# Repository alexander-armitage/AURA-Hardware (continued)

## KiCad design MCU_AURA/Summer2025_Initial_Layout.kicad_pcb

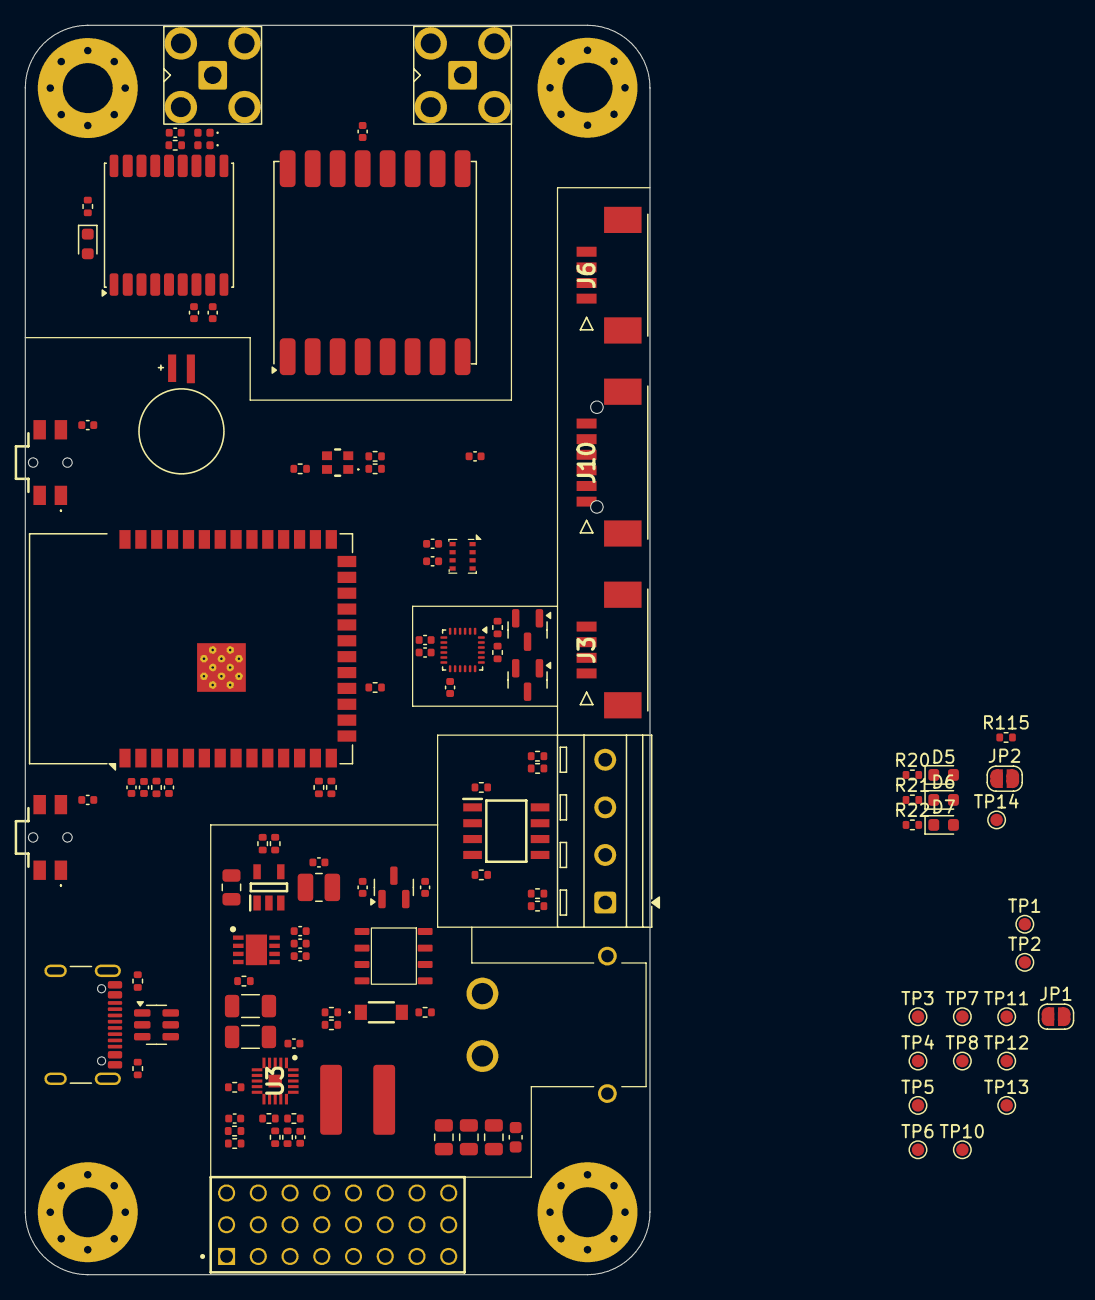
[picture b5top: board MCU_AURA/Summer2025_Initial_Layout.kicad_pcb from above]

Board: 4 copper layers, 50.0 x 100.0 mm, 123 parts (1 on the bottom side), 76 nets, no tracks yet.

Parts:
BT1: MS621FE-FL11E; BAT_MS621FE-FL11E
C22, C25, C27, C38, C39, C41, C42, C43, C44, C45, C104, C108, C109, C201, C203, C204: 100n; C_0402_1005Metric
C100, C113, C114: 1u; C_0402_1005Metric
C101, C102: 22u; C_1206_3216Metric
C103: 18n; C_0402_1005Metric
C105, C106, C107: 22u; C_0805_2012Metric
C110, C112, C202: 10u; C_0402_1005Metric
C111: 4u7; C_0805_2012Metric
C115: 100n; C_0603_1608Metric
C200: 22u; C_0402_1005Metric
D1: NH-B2020RGBA-HF; NHB2020RGBAHF
D4, D5, D6, D7: LED; LED_0603_1608Metric
D101: MMSZ5242B; MMSZ5252B
D503490: D_0402_1005Metric
H1, H2, H3, H4: MountingHole_Pad; MountingHole_4mm_Pad_Via
J1, J2: SMA_Connector
J3, J6: 532617004
J4: TF-CARD_H1.8; TFCARDH18
J5: TSW-108-07-G-T; SAMTEC_TSW-108-07-G-T
J10: 532617006
J100: XT30PW-M; XT30PWM
J101: USB_C_Receptacle_USB2.0_16P; USB_C_Receptacle_GCT_USB4105-xx-A_16P_TopMnt_Horizontal
J400: Screw_Terminal_01x04; TerminalBlock_MetzConnect_Type086_RT03404HBLC_1x04_P3.81mm_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
JP1, JP2: SolderJumper_2_Bridged; SolderJumper-2_P1.3mm_Open_RoundedPad1.0x1.5mm
L4: 27nH; LED_0402_1005Metric
L100: 1u8; CKST0603-1.5uHM
L101: 2u2; L_1008_2520Metric
Q1, Q2: BSS138; SOT-23
R18, R19, R22: 1k; R_0402_1005Metric
R20, R21: 4k7; R_0402_1005Metric
R25, R26, R27, R200, R402, R405: 10k; R_0402_1005Metric
R36: 100R; R_0402_1005Metric
R37: 120R; R_0402_1005Metric
R38: 270R; R_0402_1005Metric
R100: 100k; R_0402_1005Metric
R101: 49k; R_0402_1005Metric
R102: 13k; R_0402_1005Metric
R103: 180k; R_0402_1005Metric
R104: 33k; R_0402_1005Metric
R105: 330k; R_0402_1005Metric
R106: 110k; R_0402_1005Metric
R107: 15k; R_0402_1005Metric
R108, R109: 5k1; R_0402_1005Metric
R110: 680R; R_0402_1005Metric
R111: 540k; R_0402_1005Metric
R112: 120k; R_0402_1005Metric
R113, R115, R400, R403: 220k; R_0402_1005Metric
R114, R401, R404: 22k; R_0402_1005Metric
R201, R202: 0R; R_0402_1005Metric
S3, S4: EVQ-PUC02K; EVQPUC02K
TP1, TP2, TP3, TP4, TP5, TP6, TP7, TP8, TP10, TP11, TP12, TP13, TP14: TestPoint; TestPoint_Pad_D1.0mm
U1: SI4825DDY-T1-GE3
U2: RFM95W-868S2; HOPERF_RFM9XW_SMD
U3: TPS56C230RJER; QFN45P300X300X100-21N-D
U11: ICM-20948; InvenSense_QFN-24_3x3mm_P0.4mm
U12: BMP280; Bosch_LGA-8_2x2.5mm_P0.65mm_ClockwisePinNumbering
U13: MAX-M10S; ublox_MAX
U101: TPS2115ADRBR; SON65P300X300X100-9N-D
U102: TLV62566DBVR; SOT95P280X145-5N
U103: AP2127N-1.8; SOT-23
U200: ESP32-S3-WROOM-1
U201: USBLC6-2SC6; SOT-23-6
U400: DMN6040SSD-13; SOIC127P600X170-8N

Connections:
+1V8: C42.1, C45.1, C114.1, Q1.1 (G), Q2.1 (G), R26.2, R27.2, TP11.1, U11.8 (VDDIO), U11.13 (VDD), U11.22 (~CS), U103.2 (VO)
+3V3: C22.1, C25.1, C27.1, C38.1, C39.1, C44.1, C112.1, C113.1, C200.1, C201.1, D1.3 (VIN), D7.2 (A), J3.1, J4.4 (VDD), J10.1, L101.2, R25.2, R111.2, R200.2, TP13.1, U2.13 (3.3V), U12.2 (CSB), U12.6 (VDDIO), U12.8 (VDD), U13.7 (VCC_IO), U13.8 (VCC), U103.3 (VI), U200.2 (3V3)
+5V: C105.1, C106.1, C107.1, C109.1, C115.1, D5.2 (A), J5.02, J5.05, J5.08, J5.11, J5.14, J5.17, J5.20, J5.23, JP1.1 (A), L100.2, R106.2, TP6.1, U101.6 (IN2)
+5V_FILT: C110.1, C111.1, D6.2 (A), JP1.2 (B), JP2.2 (B), TP8.1, U101.7 (OUT), U102.1 (EN/PG), U102.4 (VIN)
+BATT: J100.1, J400.2, J400.4, U1.1, U1.2, U1.3
+BATT_FILT: C101.1, C102.1, D101.1 (K), R101.2, R113.2, U1.5, U1.6, U1.7, U1.8, U3.2 (VIN_1), U3.3 (VIN_2), U3.4 (VIN_3), U3.5 (VIN_4)
+VCC_RF: R19.2, U13.14 (VCC_RF)
+VUSB: C108.1, J101.A4 (VBUS), J101.A9 (VBUS), J101.B4 (VBUS), J101.B9 (VBUS), JP2.1 (A), R115.2, TP10.1, U101.3 (D1), U101.8 (IN1), U201.5 (VBUS)
/Actuation Control/GND_PY1: J400.1, R400.2, U400.7, U400.8
/Actuation Control/GND_PY2: J400.3, R403.2, U400.5, U400.6
/Digital_Peripherals/REGOUT: C41.1, U11.10 (REGOUT)
/Digital_Peripherals/SCL_1V8: Q1.2 (S), R26.1, TP1.1, U11.23 (SCL/SCLK)
/Digital_Peripherals/SDA_1V8: Q2.2 (S), R27.1, TP2.1, U11.24 (SDA/SDI)
/ESP32/D+: R202.2, U200.14 (USB_D+)
/ESP32/D-: R201.2, U200.13 (USB_D-)
/ESP32/EN: C202.1, C204.1, R200.1, S4.3 (NO_2), U200.3 (EN)
/ESP32/RST: C203.1, S3.3 (NO_2), U200.27 (IO0)
/ESP32/USB_MCU_D+: R202.1, U201.4 (I/O2)
/ESP32/USB_MCU_D-: R201.1, U201.6 (I/O1)
/Power/3V3_LED: D7.1 (K), R22.2
/Power/5V_FILT_LED: D6.1 (K), R21.2
/Power/5V_LED: D5.1 (K), R20.2
/Power/BST_5V: C104.1, U3.1 (BST)
/Power/CC1: J101.A5 (CC1), R108.2
/Power/CC2: J101.B5 (CC2), R109.2
/Power/EN_5V: R101.1, R102.2, TP4.1, U3.12 (EN)
/Power/FB_3V3: R111.1, R112.2, TP12.1, U102.5 (FB)
/Power/FB_5V: R106.1, R107.2, TP5.1, U3.14 (FB)
/Power/MODE: R103.1, R104.2, U3.15 (MODE)
/Power/PGOOD: R105.1, TP3.1, U3.9 (PGOOD)
/Power/SS_5V: C103.1, U3.11 (SS)
/Power/SW_3V3: L101.1, U102.3 (SW)
/Power/SW_5V: C104.2, L100.1, U3.6 (SW_1), U3.19 (SW_2), U3.20 (SW_3)
/Power/VCC: C100.1, R103.2, R105.2, U3.17 (VCC)
/Power/rvrs_plr: D101.2 (A), R100.2, TP7.1, U1.4
/RF_Peripherals/GPS_IND: C43.1, L4.2, R19.1
/RF_Peripherals/GPS_LED: D4.1 (K), R18.2
/RF_Peripherals/GPS_RF_IN: D503490.1 (K1), J2.1, L4.1, U13.11 (RF_IN)
/RF_Peripherals/LOCK_PULSE: D4.2 (A), U13.4 (TIMEPULSE)
/RF_Peripherals/LORA_ANT: J1.1, U2.9 (ANT)
CARD_DETECT: J4.CD1 (CARD_DETEC), U200.20 (IO12)
CONT_1: R400.1, R401.2, U200.31 (IO38)
CONT_2: R403.1, R404.2, U200.26 (IO45)
EXT_CS: J10.5, U200.19 (IO11)
GND: C22.2, C25.2, C27.2, C38.2, C39.2, C41.2, C42.2, C43.2, C44.2, C45.2, C100.2, C101.2, C102.2, C103.2, C105.2, C106.2, C107.2, C108.2, C109.2, C110.2, C111.2, C112.2, C113.2, C114.2, C115.2, C200.2, C201.2, C202.2, C203.2, C204.2, D503490.2 (K2), J1.2, J2.2, J3.4, J4.6 (VSS), J4.G1 (GND_1), J4.G2 (GND_2), J4.G3 (GND_3), J4.G4 (GND_4), J5.01, J5.04, J5.07, J5.10, J5.13, J5.16, J5.19, J5.22, J10.6, J100.2, J100.3, J100.4, J101.A1 (GND), J101.A12 (GND), J101.B1 (GND), J101.B12 (GND), R18.1, R20.1, R21.1, R22.1, R36.1, R37.1, R38.1, R100.1, R102.1, R104.1, R107.1, R108.1, R109.1, R110.1, R112.1, R114.1, R115.1, R401.1, R402.1, R404.1, R405.1, S3.2 (COM_1), S4.2 (COM_1), U2.1 (GND), U2.8 (GND), U2.10 (GND), U3.7 (PGND_1), U3.8 (PGND_2), U3.10 (NC_1), U3.13 (AGND), U3.16 (NC_2), U3.18 (PGND_3), U3.21 (PGND_4), U11.9 (SDO/AD0), U11.11 (FSYNC), U11.18 (GND), U11.20 (GND), U12.1 (GND), U12.5 (SDO), U12.7 (GND), U13.1 (GND), U13.10 (GND), U13.12 (GND), U101.2 (D0), U101.5 (GND_1), U101.9 (GND_2), U102.2 (GND), U103.1 (GND), U200.1 (GND), U200.40 (GND), U200.41 (GND), U201.2 (GND), U400.1, U400.3
GPS_INT: U13.5 (EXTINT), U200.10 (IO17)
LED_B: D1.2 (BLUE), R36.2, U200.25 (IO48)
LED_G: D1.4 (GREEN), R37.2, U200.24 (IO47)
LED_R: D1.1 (RED), R38.2, U200.16 (IO46)
LORA_CS: U2.5 (NSS), U200.7 (IO7)
LORA_RST: U2.6 (RESET), U200.12 (IO8)
MISO: J4.7 (DAT0), J10.3, U2.2 (MISO), U200.29 (IO36)
MOSI: J4.3 (CMD), J10.2, U2.3 (MOSI), U200.28 (IO35)
MSFT_1: R402.2, U400.2
MSFT_2: R405.2, U400.4
unnamed: R110.2, U101.4 (ILIM)
unnamed: TP14.1, U101.1 (STAT)
RX: U13.2 (TXD), U200.36 (RXD0)
SCK: J4.5 (CLK), J10.4, U2.4 (SCK), U200.30 (IO37)
SCL: J3.2, Q1.3 (D), U12.4 (SCK), U200.8 (IO15)
SDA: J3.3, Q2.3 (D), U12.3 (SDI), U200.9 (IO16)
SD_CS: J4.2 (CD/DAT3), R25.1, U200.18 (IO10)
SERVO_1: J5.03, U200.39 (IO1)
SERVO_2: J5.06, U200.38 (IO2)
SERVO_3: J5.09, U200.15 (IO3)
SERVO_4: J5.12, U200.4 (IO4)
SERVO_5: J5.15, U200.5 (IO5)
SERVO_6: J5.18, U200.6 (IO6)
TCK: J6.1, U200.32 (IO39)
TDI: J6.3, U200.34 (IO41)
TDO: J6.2, U200.33 (IO40)
TMS: J6.4, U200.35 (IO42)
TX: U13.3 (RXD), U200.37 (TXD0)
USB_D+: J101.A6 (D+), J101.B6 (D+), U201.3 (I/O2)
USB_D-: J101.A7 (D-), J101.B7 (D-), U201.1 (I/O1)
VBAT: R113.1, R114.2, U200.21 (IO13)

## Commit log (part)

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2025-06-02 Started Editing
    Problem syncing desktop to laptop (libraries).
2025-06-03 Added Samacsys libraries
    Made the libraries from the component search engine local.
2025-06-03 Final libraries added.
    Entire project should now be linked.
2025-06-03 Synchronised
2025-06-03 Adding 3D Models
2025-06-03 All CAD models synchronised
2025-06-03 Adding Connectors
2025-06-05 Initial Schematic Draft
2025-06-06 Initial draft
2025-06-10 Started Routing
2025-06-11 First fully routed version
2025-06-12 First version
2025-06-16 New PDB specs chosen
2025-06-19 Moving to laptop
2025-06-20 Annotated schematic for PDB
2025-06-20 Second Layout Attempt
    Renamed all components and placed them all.
2025-06-21 Started Routing 2
    Forgot to save the pcb.
2025-06-21 Continued Routing
2025-06-22 First PDB Version
2025-06-25 Second Iteration
2025-06-28 Replaced JTAG with Flash
    JTAG is used through USB so a Flash chip was added to MCU. PDB is just being cleaned up currently.
2025-06-28 Fixed LM2514 Layout
    Followed datasheet guidelines for the SW and HO traces.
2025-06-29 New Component Values
2025-07-01 Re Routing some of the power board
    Connectors had positive and negative the wrong way around, and some of the routing did not look good.
2025-07-05 First review for PDB.
2025-07-07 Second Iteration MCU
2025-07-08 Second iteration PDB
2025-07-10 PDB organised
2025-07-10 Production Files
2025-07-11 Production Files for MCU
2025-07-11 CPL file finalised for MCU
2025-07-12 Silk Screen Done
2025-07-13 First Order
2025-07-24 SD Card Models
2025-09-01 Deleted old files
2025-09-01 Create solder pad footprints
2025-09-01 Synchronised project outline and block diagram
2025-09-01 Tidied up PDB schematic for documentation.
2025-09-01 Added exported schematic PDFs
2025-09-01 Started ReadMe.
    The readme is still a work in progress and is not finished!
2025-09-07 Update README.md
    Added project repository structure.
2025-10-29 Initial FPGA Commit
2025-11-13 Power regulation started
    Started doing research into the project to see what needs to be done
2025-11-15 Initial component selection done
2025-12-20 Added USB power schottky and started DDR3L
    Transferring from laptop to PC to decide DDR3 pins.
2025-12-25 Moving progress to laptop.
    Started to decide on BGA fanout for DDR. Next is for the FPGA and to assign byte lanes to DQ.
2025-12-25 Moving to PC.
    Placed the VTT termination resistors roughly, rotated the DDR IC 180, and deleted the initial draft of routing.
2025-12-28 Delete
2025-12-28 Added and modified libraries
2025-12-28 Added Connectors, FPGA Power and organized sheets.
    All schematic sheets now go up in order with the correct prefix.
2025-12-28 Renamed the files to not have the prefix.
2026-02-15 Following new DDR3 reference
    Using Scopefun v2 as a reference design for the XC7A35T-FTG256
2026-03-30 Moved to KiCAD V10 for delay.
    The FPGA PCB has now been moved to KiCAD V10 to make use of the new delay features and design rules are being setup.
    PCB stack-up has now been decided.
2026-03-31 Time domain tuning setup.
    The tuning profiles and net classes have been setup to enable time domain tuning.
2026-04-14 Recovery after being partially deleted.
    Revert to prior than this if this version is broken due to OneDrive sync issue.
2026-05-16 Fixed delay matching issue and started data lines
    The delay matching is now working again and the data byte lanes are in the process of being routed.
2026-06-20 Changing stackup to 10 layers and connectors change
    Development has been slow due to SI concerns with 8 layers so changing the layer count to 10 will simplify design. The picoblade/SD connector(s) are large and not high speed, so a high speed mezzanin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
2026-06-21 Continuing the FTDI
